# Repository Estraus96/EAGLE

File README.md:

# EAGLE

The purpose of this repository is to share designs made in EAGLE on Hardware for use with open source applications.

I do this as Hobby because I like it and it turns me on

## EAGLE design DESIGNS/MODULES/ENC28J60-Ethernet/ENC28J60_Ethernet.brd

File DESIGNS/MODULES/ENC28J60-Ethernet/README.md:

# ENC28J60 WITH ETHERNET

This Design will be use on more famous modules of ethernet to SPI like [this](https://core-electronics.com.au/enc28j60-ethernet-lan-network-module.html)

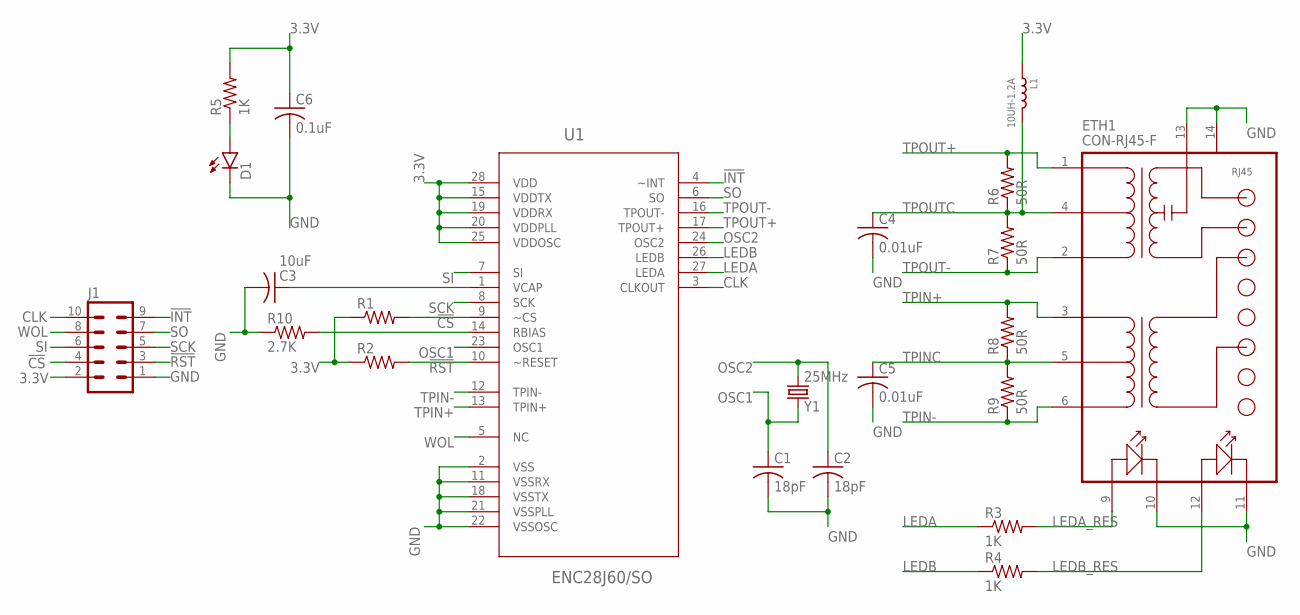
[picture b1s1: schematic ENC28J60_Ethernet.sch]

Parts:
C1, C2: 18pF; C0805
C3: 10uF; C1210
C4, C5: 0.01uF; C0805
C6: 0.1uF; C0805
D1: LEDCHIP-LED0805; CHIP-LED0805
ETH1: CON-RJ45-F; HR911105A
J1: MA05-2
L1: 10UH-1.2A; L0805
R1, R2: R-US_R0805; R0805
R3, R4, R5: 1K; R0805
R6, R7, R8, R9: 50R; R0805
R10: 2.7K; R0805
U1: ENC28J60/SO; SOIC127P1034X264-28N
Y1: 25MHz; HC49/S

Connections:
3.3V: C6.1, J1.2, L1.1, R1.1, R2.1, R5.2, U1.15 (VDDTX), U1.19 (VDDRX), U1.20 (VDDPLL), U1.25 (VDDOSC), U1.28 (VDD)
!CS!: J1.4, R1.2, U1.9 (~CS)
!INT!: J1.9, U1.4 (~INT)
!RST!: J1.3, R2.2, U1.10 (~RESET)
CLK: J1.10, U1.3 (CLKOUT)
GND: C1.2, C2.2, C3.2, C4.2, C5.2, C6.2, D1.C, ETH1.10, ETH1.11, ETH1.13, ETH1.14, J1.1, R10.1, U1.2 (VSS), U1.11 (VSSRX), U1.18 (VSSTX), U1.21 (VSSPLL), U1.22 (VSSOSC)
LEDA: R3.1, U1.27 (LEDA)
LEDA_RES: ETH1.9, R3.2
LEDB: R4.1, U1.26 (LEDB)
LEDB_RES: ETH1.12, R4.2
unnamed: D1.A, R5.1
OSC1: C1.1, U1.23 (OSC1), Y1.1
OSC2: C2.1, U1.24 (OSC2), Y1.2
RBIAS: R10.2, U1.14 (RBIAS)
SCK: J1.5, U1.8 (SCK)
SI: J1.6, U1.7 (SI)
SO: J1.7, U1.6 (SO)
TPIN+: ETH1.3, R8.2, U1.13 (TPIN+)
TPIN-: ETH1.6, R9.1, U1.12 (TPIN-)
TPINC: C5.1, ETH1.5, R8.1, R9.2
TPOUT+: ETH1.1, R6.2, U1.17 (TPOUT+)
TPOUT-: ETH1.2, R7.1, U1.16 (TPOUT-)
TPOUTC: C4.1, ETH1.4, L1.2, R6.1, R7.2
VCAP: C3.1, U1.1 (VCAP)
WOL: J1.8, U1.5 (NC)

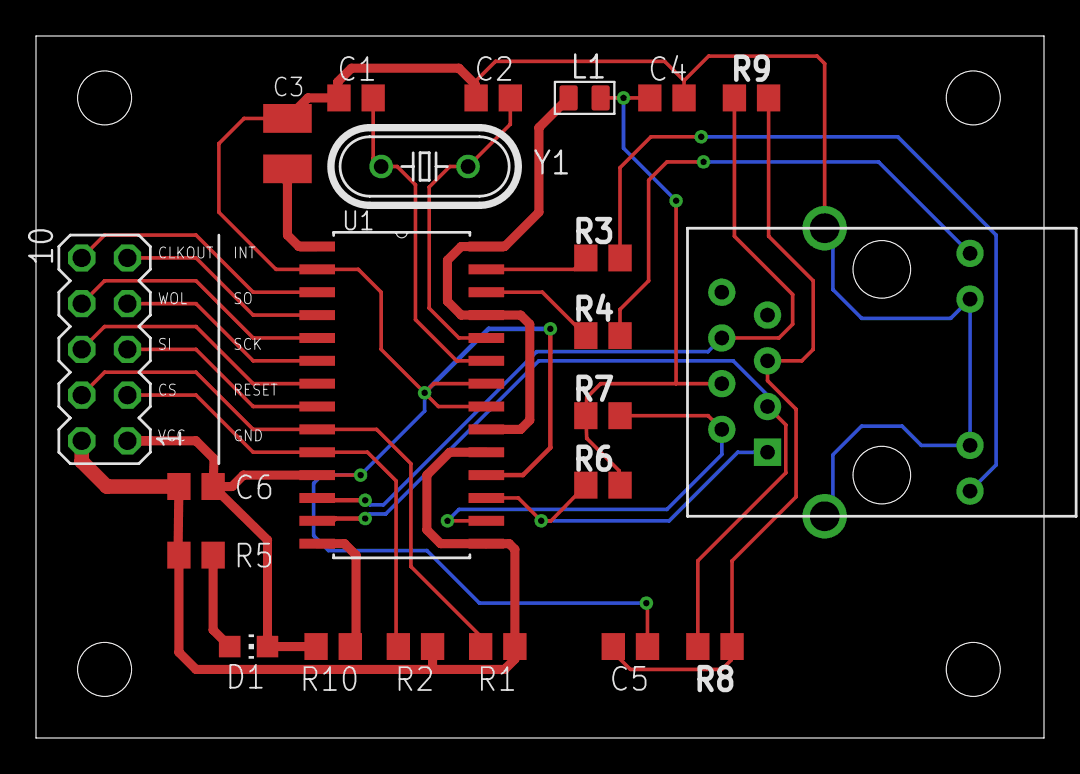
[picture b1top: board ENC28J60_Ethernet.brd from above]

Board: 2 copper layers, 56.0 x 39.0 mm, 22 parts (0 on the bottom side), 25 nets.

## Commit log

2019-06-18 Create ENC28J60-Ethernet
2019-06-18 Create temp
2019-06-18 Rename Info.md to README.md
